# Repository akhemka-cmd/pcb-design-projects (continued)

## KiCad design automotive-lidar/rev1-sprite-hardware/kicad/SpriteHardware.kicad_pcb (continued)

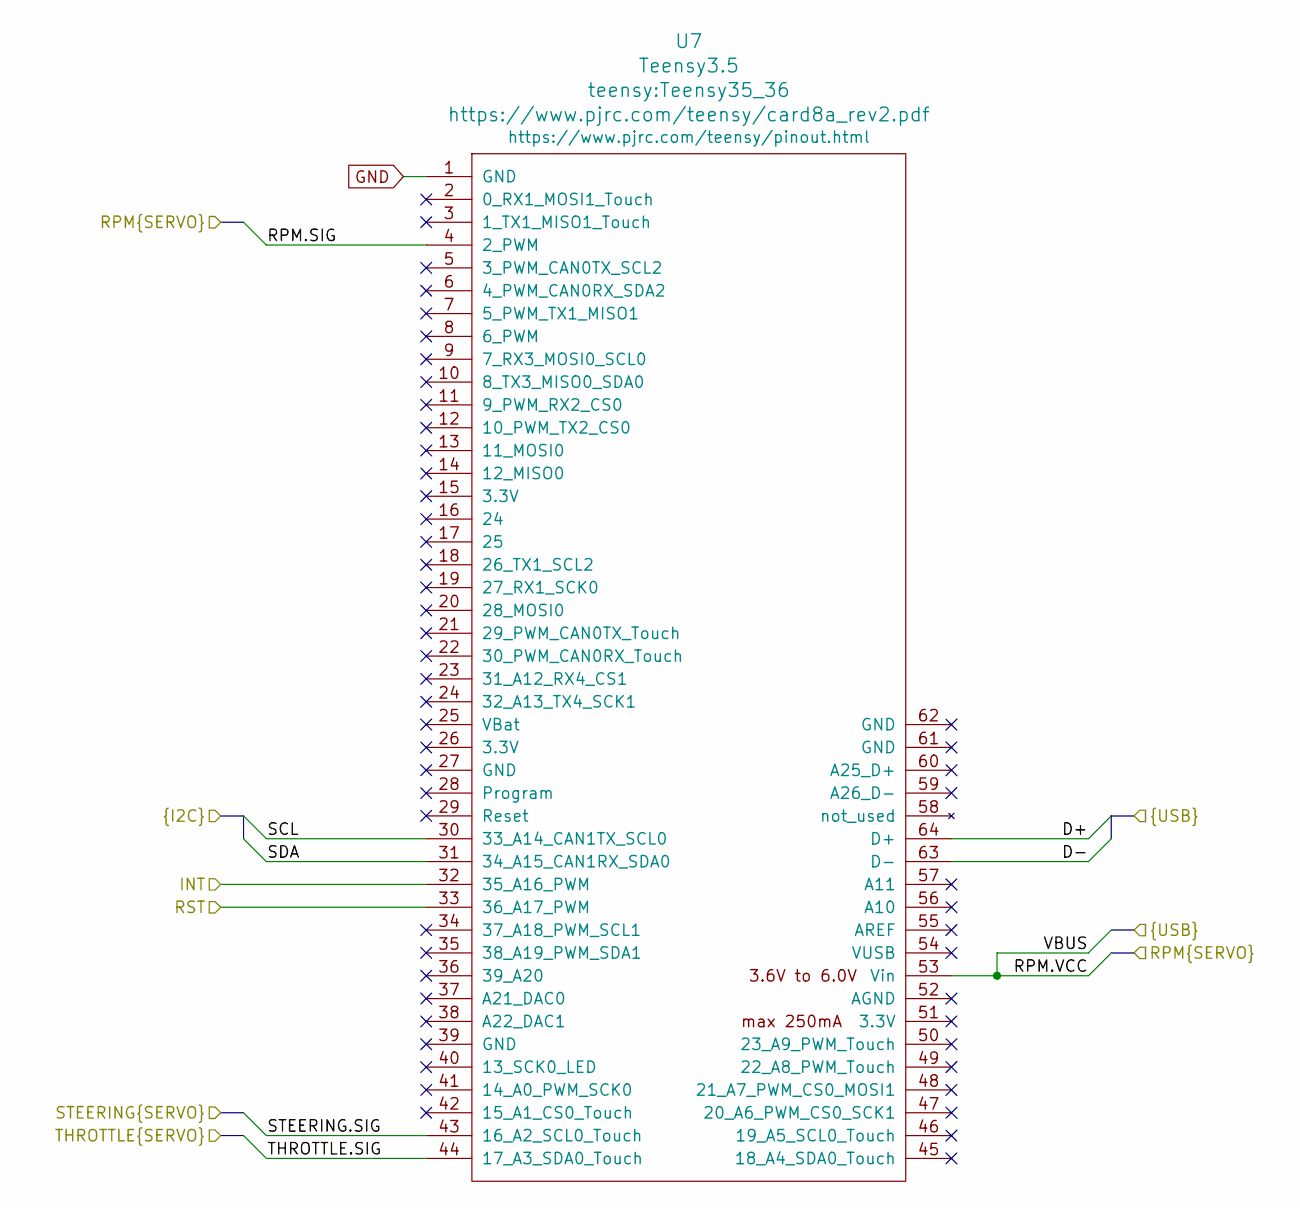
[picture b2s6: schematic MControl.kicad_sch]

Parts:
U7: Teensy3.5; Teensy35_36

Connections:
/Interface Board/IMU_I2C.SCL: U7.30 (33_A14_CAN1TX_SCL0); also elsewhere on the board
/Interface Board/IMU_I2C.SDA: U7.31 (34_A15_CAN1RX_SDA0); also elsewhere on the board
/Interface Board/IMU_INT: U7.32 (35_A16_PWM); also elsewhere on the board
/Interface Board/IMU_RST: U7.33 (36_A17_PWM); also elsewhere on the board
/Interface Board/STEERING.SIG: U7.43 (16_A2_SCL0_Touch); also elsewhere on the board
/Interface Board/THROTTLE.SIG: U7.44 (17_A3_SDA0_Touch); also elsewhere on the board
/Interface Board/USB_M.D+: U7.64 (D+); also elsewhere on the board
/Interface Board/USB_M.D-: U7.63 (D-); also elsewhere on the board
/WIM3.SIG: U7.4 (2_PWM); also elsewhere on the board
/WIM3.VCC: U7.53 (Vin); also elsewhere on the board
GND: U7.1 (GND); also elsewhere on the board

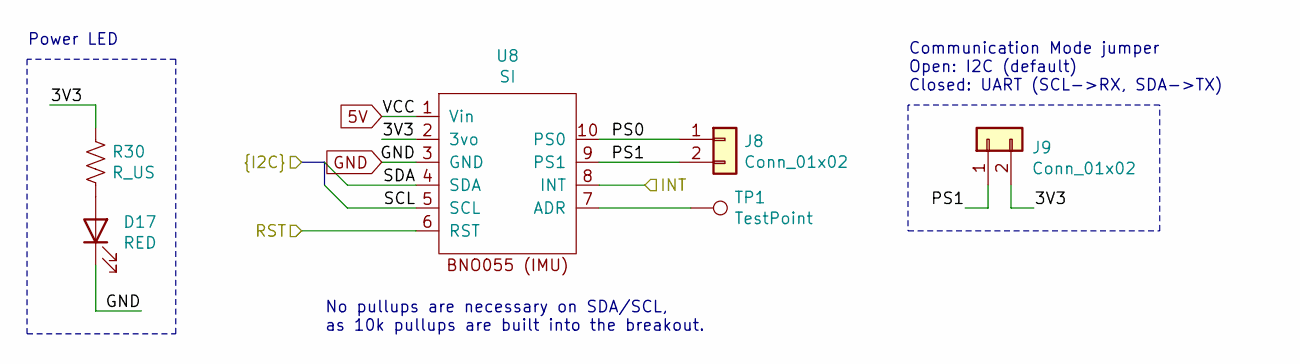
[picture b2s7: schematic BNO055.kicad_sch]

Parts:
D17: RED; LED_0603_1608Metric_Pad1.05x0.95mm_HandSolder
J8, J9: Conn_01x02; PinHeader_1x02_P2.54mm_Vertical
R30: R_US; R_0603_1608Metric_Pad1.05x0.95mm_HandSolder
TP1: TestPoint; TestPoint_Plated_Hole_D2.0mm
U8: SI

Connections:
5V: U8.1 (Vin); also elsewhere on the board
/Interface Board/BNO055 (IMU)/3V3: J9.2, R30.1, U8.2 (3vo)
/Interface Board/BNO055 (IMU)/PS0: J8.1, U8.10 (PS0)
/Interface Board/BNO055 (IMU)/PS1: J8.2, J9.1, U8.9 (PS1)
/Interface Board/IMU_I2C.SCL: U8.5 (SCL); also elsewhere on the board
/Interface Board/IMU_I2C.SDA: U8.4 (SDA); also elsewhere on the board
/Interface Board/IMU_INT: U8.8 (INT); also elsewhere on the board
/Interface Board/IMU_RST: U8.6 (RST); also elsewhere on the board
GND: D17.1 (K), U8.3 (GND); also elsewhere on the board
unnamed: D17.2 (A), R30.2
unnamed: TP1.1, U8.7 (ADR)

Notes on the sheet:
Communication Mode jumper Open: I2C (default) Closed: UART (SCL->RX, SDA->TX)
Power LED
No pullups are necessary on SDA/SCL, as 10k pullups are built into the breakout.

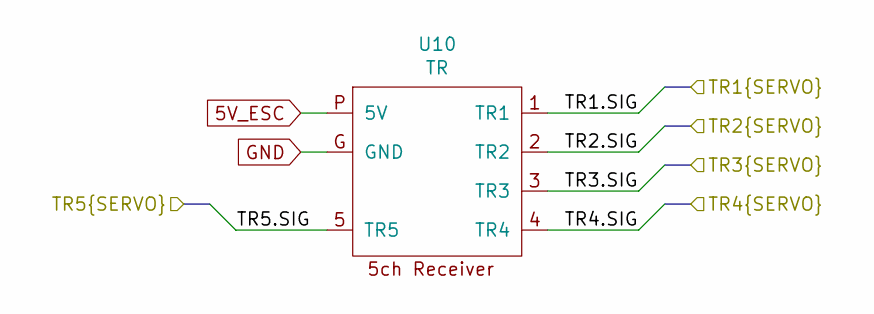
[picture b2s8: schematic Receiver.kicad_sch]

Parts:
U10: TR

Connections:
5V_ESC: U10.P (5V); also elsewhere on the board
/Interface Board/IM2A.SIG: U10.2 (TR2); also elsewhere on the board
/Interface Board/IM3A.SIG: U10.3 (TR3); also elsewhere on the board
/Interface Board/TR1.SIG: U10.1 (TR1); also elsewhere on the board
/Interface Board/TR4.SIG: U10.4 (TR4)
/Interface Board/TR5.SIG: U10.5 (TR5)
GND: U10.G (GND); also elsewhere on the board

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
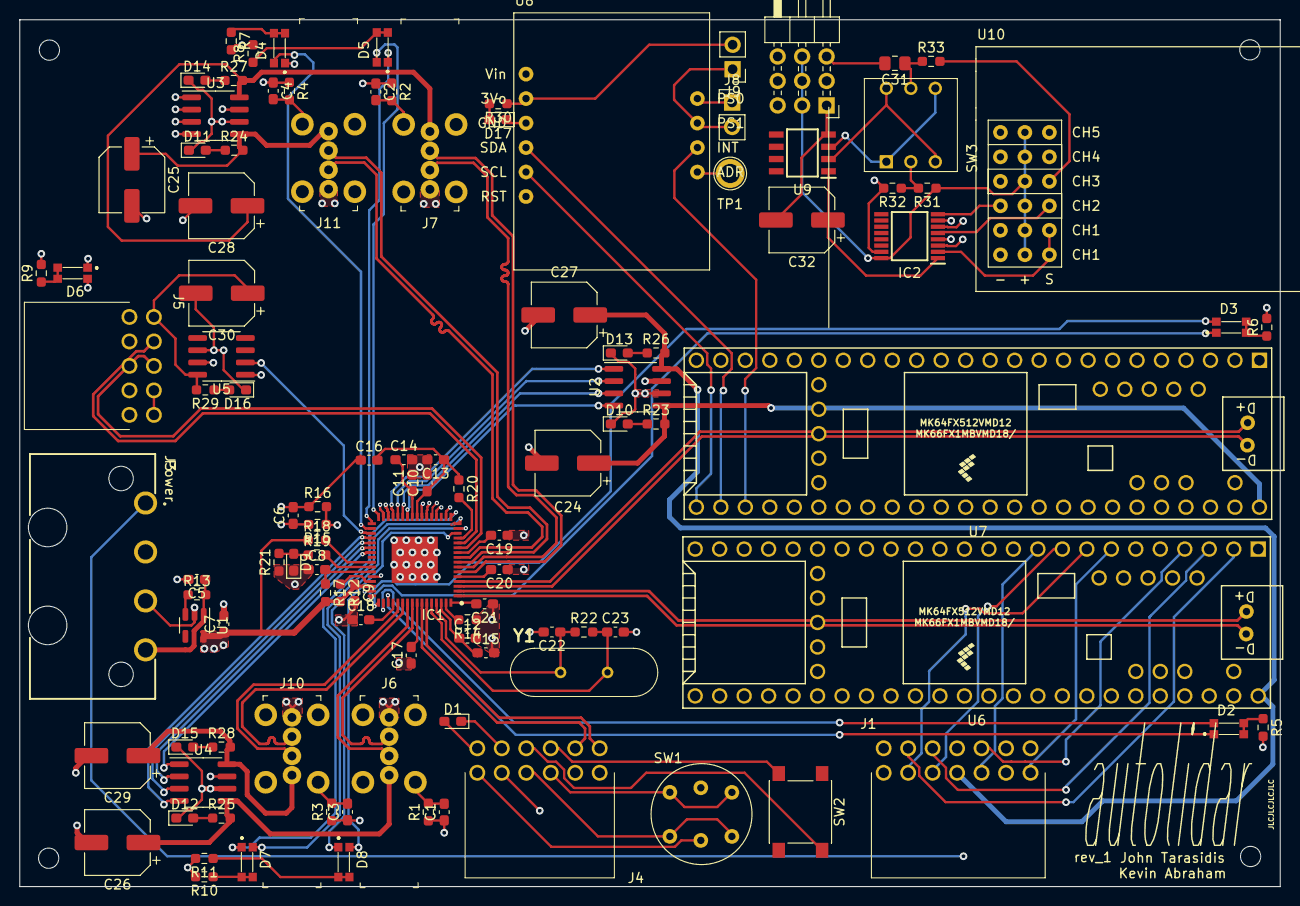
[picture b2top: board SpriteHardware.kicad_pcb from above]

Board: 4 copper layers, 130.8 x 89.9 mm, 110 parts (0 on the bottom side), 126 nets.
